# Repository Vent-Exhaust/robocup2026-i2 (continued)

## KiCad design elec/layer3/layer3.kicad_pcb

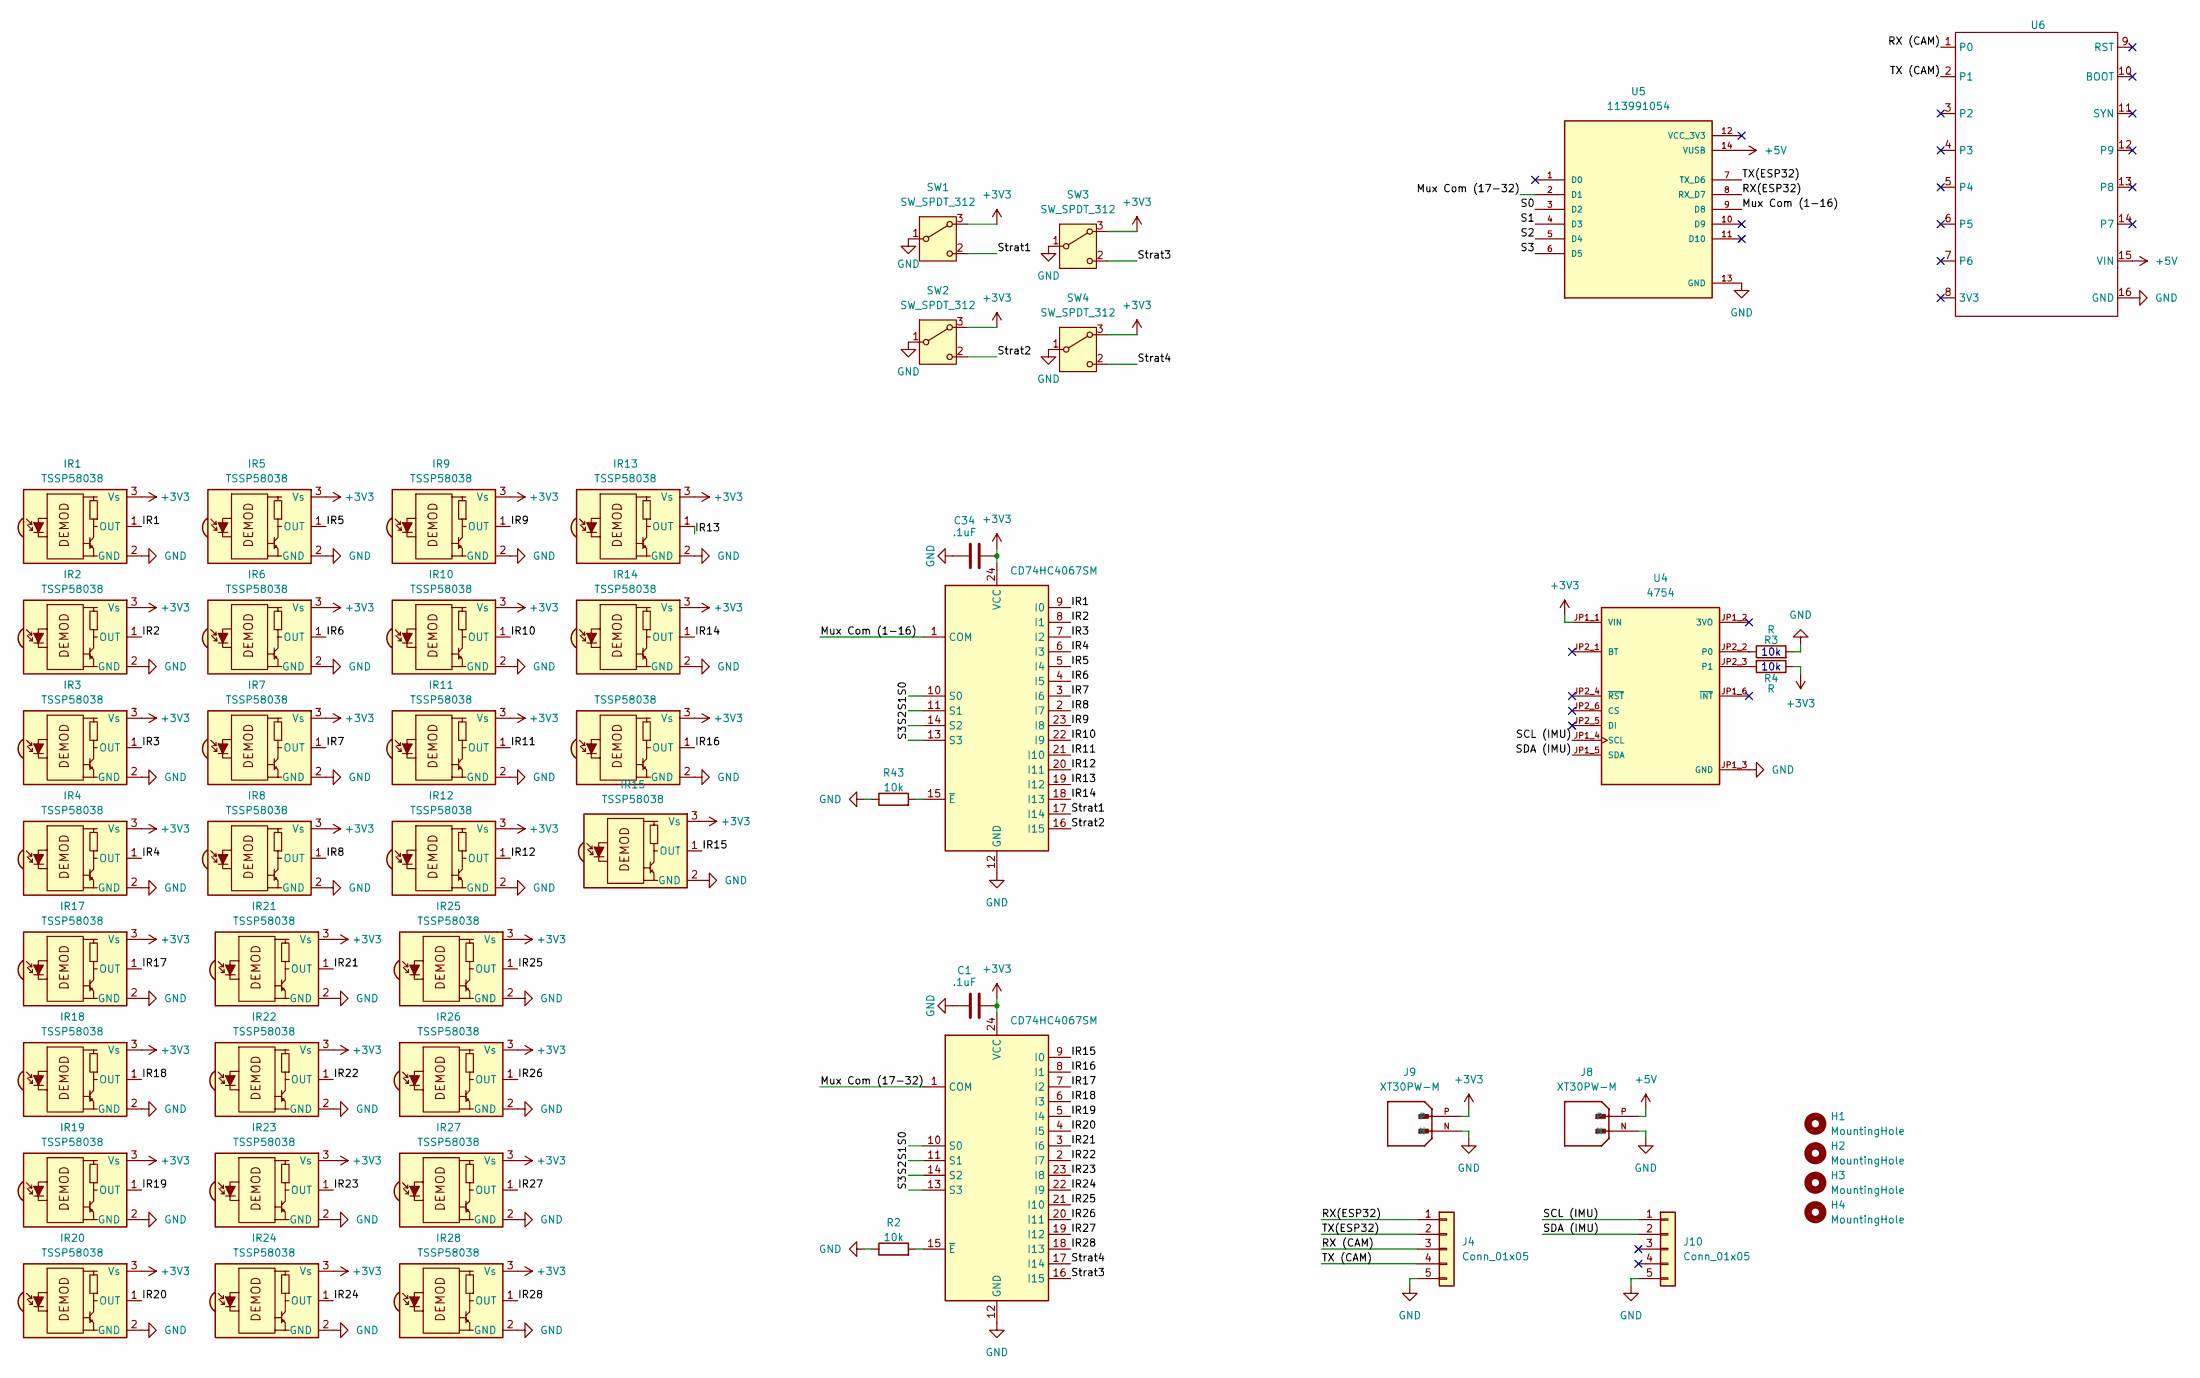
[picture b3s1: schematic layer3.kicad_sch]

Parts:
C1, C34: .1uF; C_0603_1608Metric
H1, H2, H3, H4: MountingHole; MountingHole_3.2mm_M3_DIN965_Pad
IR1, IR2, IR3, IR4, IR5, IR6, IR7, IR8, IR9, IR10, IR11, IR12, IR13, IR14, IR15, IR16, IR17, IR18, IR19, IR20, IR21, IR22, IR23, IR24, IR25, IR26, IR27, IR28: TSSP58038; Vishay_MINICAST-3Pin
J4, J10: Conn_01x05; JST_XH_B5B-XH-A_1x05_P2.50mm_Vertical
J8, J9: XT30PW-M; AMASS_XT30UPB-M_1x02_P5.0mm_Vertical; PARTREV 1.2
R2, R43: 10k; R_0603_1608Metric
R3, R4: R; R_0603_1608Metric_Pad0.98x0.95mm_HandSolder
SW1, SW2, SW3, SW4: SW_SPDT_312; SS12D00G3
U1, U2: CD74HC4067SM
U4: 4754; MODULE_4754; PARTREV 2021-03-16
U5: 113991054; XiaoSeeedStudioEsp32; PARTREV 23/05/2022
U6: OPENMV_M7

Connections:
+3V3: C1.2, C34.2, IR1.3 (Vs), IR2.3 (Vs), IR3.3 (Vs), IR4.3 (Vs), IR5.3 (Vs), IR6.3 (Vs), IR7.3 (Vs), IR8.3 (Vs), IR9.3 (Vs), IR10.3 (Vs), IR11.3 (Vs), IR12.3 (Vs), IR13.3 (Vs), IR14.3 (Vs), IR15.3 (Vs), IR16.3 (Vs), IR17.3 (Vs), IR18.3 (Vs), IR19.3 (Vs), IR20.3 (Vs), IR21.3 (Vs), IR22.3 (Vs), IR23.3 (Vs), IR24.3 (Vs), IR25.3 (Vs), IR26.3 (Vs), IR27.3 (Vs), IR28.3 (Vs), J9.P, R4.1, SW1.3 (A), SW2.3 (A), SW3.3 (A), SW4.3 (A), U1.24 (VCC), U2.24 (VCC), U4.JP1_1 (VIN)
+5V: J8.P, U5.14 (VUSB), U6.15 (VIN)
/IR1: IR1.1 (OUT), U2.9 (I0)
/IR2: IR2.1 (OUT), U2.8 (I1)
/IR3: IR3.1 (OUT), U2.7 (I2)
/IR4: IR4.1 (OUT), U2.6 (I3)
/IR5: IR5.1 (OUT), U2.5 (I4)
/IR6: IR6.1 (OUT), U2.4 (I5)
/IR7: IR7.1 (OUT), U2.3 (I6)
/IR8: IR8.1 (OUT), U2.2 (I7)
/IR9: IR9.1 (OUT), U2.23 (I8)
/IR10: IR10.1 (OUT), U2.22 (I9)
/IR11: IR11.1 (OUT), U2.21 (I10)
/IR12: IR12.1 (OUT), U2.20 (I11)
/IR13: IR13.1 (OUT), U2.19 (I12)
/IR14: IR14.1 (OUT), U2.18 (I13)
/IR15: IR15.1 (OUT), U1.9 (I0)
/IR16: IR16.1 (OUT), U1.8 (I1)
/IR17: IR17.1 (OUT), U1.7 (I2)
/IR18: IR18.1 (OUT), U1.6 (I3)
/IR19: IR19.1 (OUT), U1.5 (I4)
/IR20: IR20.1 (OUT), U1.4 (I5)
/IR21: IR21.1 (OUT), U1.3 (I6)
/IR22: IR22.1 (OUT), U1.2 (I7)
/IR23: IR23.1 (OUT), U1.23 (I8)
/IR24: IR24.1 (OUT), U1.22 (I9)
/IR25: IR25.1 (OUT), U1.21 (I10)
/IR26: IR26.1 (OUT), U1.20 (I11)
/IR27: IR27.1 (OUT), U1.19 (I12)
/IR28: IR28.1 (OUT), U1.18 (I13)
/Mux Com (1-16): U2.1 (COM), U5.9 (D8)
/Mux Com (17-32): U1.1 (COM), U5.2 (D1)
/RX (CAM): J4.3, U6.1 (P0)
/RX(ESP32): J4.1, U5.8 (RX_D7)
/S0: U1.10 (S0), U2.10 (S0), U5.3 (D2)
/S1: U1.11 (S1), U2.11 (S1), U5.4 (D3)
/S2: U1.14 (S2), U2.14 (S2), U5.5 (D4)
/S3: U1.13 (S3), U2.13 (S3), U5.6 (D5)
/SCL (IMU): J10.1, U4.JP1_4 (SCL)
/SDA (IMU): J10.2, U4.JP1_5 (SDA)
/Strat1: SW1.2 (C), U2.17 (I14)
/Strat2: SW2.2 (C), U2.16 (I15)
/Strat3: SW3.2 (C), U1.16 (I15)
/Strat4: SW4.2 (C), U1.17 (I14)
/TX (CAM): J4.4, U6.2 (P1)
/TX(ESP32): J4.2, U5.7 (TX_D6)
GND: C1.1, C34.1, IR1.2 (GND), IR2.2 (GND), IR3.2 (GND), IR4.2 (GND), IR5.2 (GND), IR6.2 (GND), IR7.2 (GND), IR8.2 (GND), IR9.2 (GND), IR10.2 (GND), IR11.2 (GND), IR12.2 (GND), IR13.2 (GND), IR14.2 (GND), IR15.2 (GND), IR16.2 (GND), IR17.2 (GND), IR18.2 (GND), IR19.2 (GND), IR20.2 (GND), IR21.2 (GND), IR22.2 (GND), IR23.2 (GND), IR24.2 (GND), IR25.2 (GND), IR26.2 (GND), IR27.2 (GND), IR28.2 (GND), J4.5, J8.N, J9.N, J10.5, R2.1, R3.2, R43.1, SW1.1 (B), SW2.1 (B), SW3.1 (B), SW4.1 (B), U1.12 (GND), U2.12 (GND), U4.JP1_3 (GND), U5.13 (GND), U6.16 (GND)
unnamed: R2.2, U1.15 (~E)
unnamed: R43.2, U2.15 (~E)
unnamed: R3.1, U4.JP2_2 (P0)
unnamed: R4.2, U4.JP2_3 (P1)

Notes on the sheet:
10k

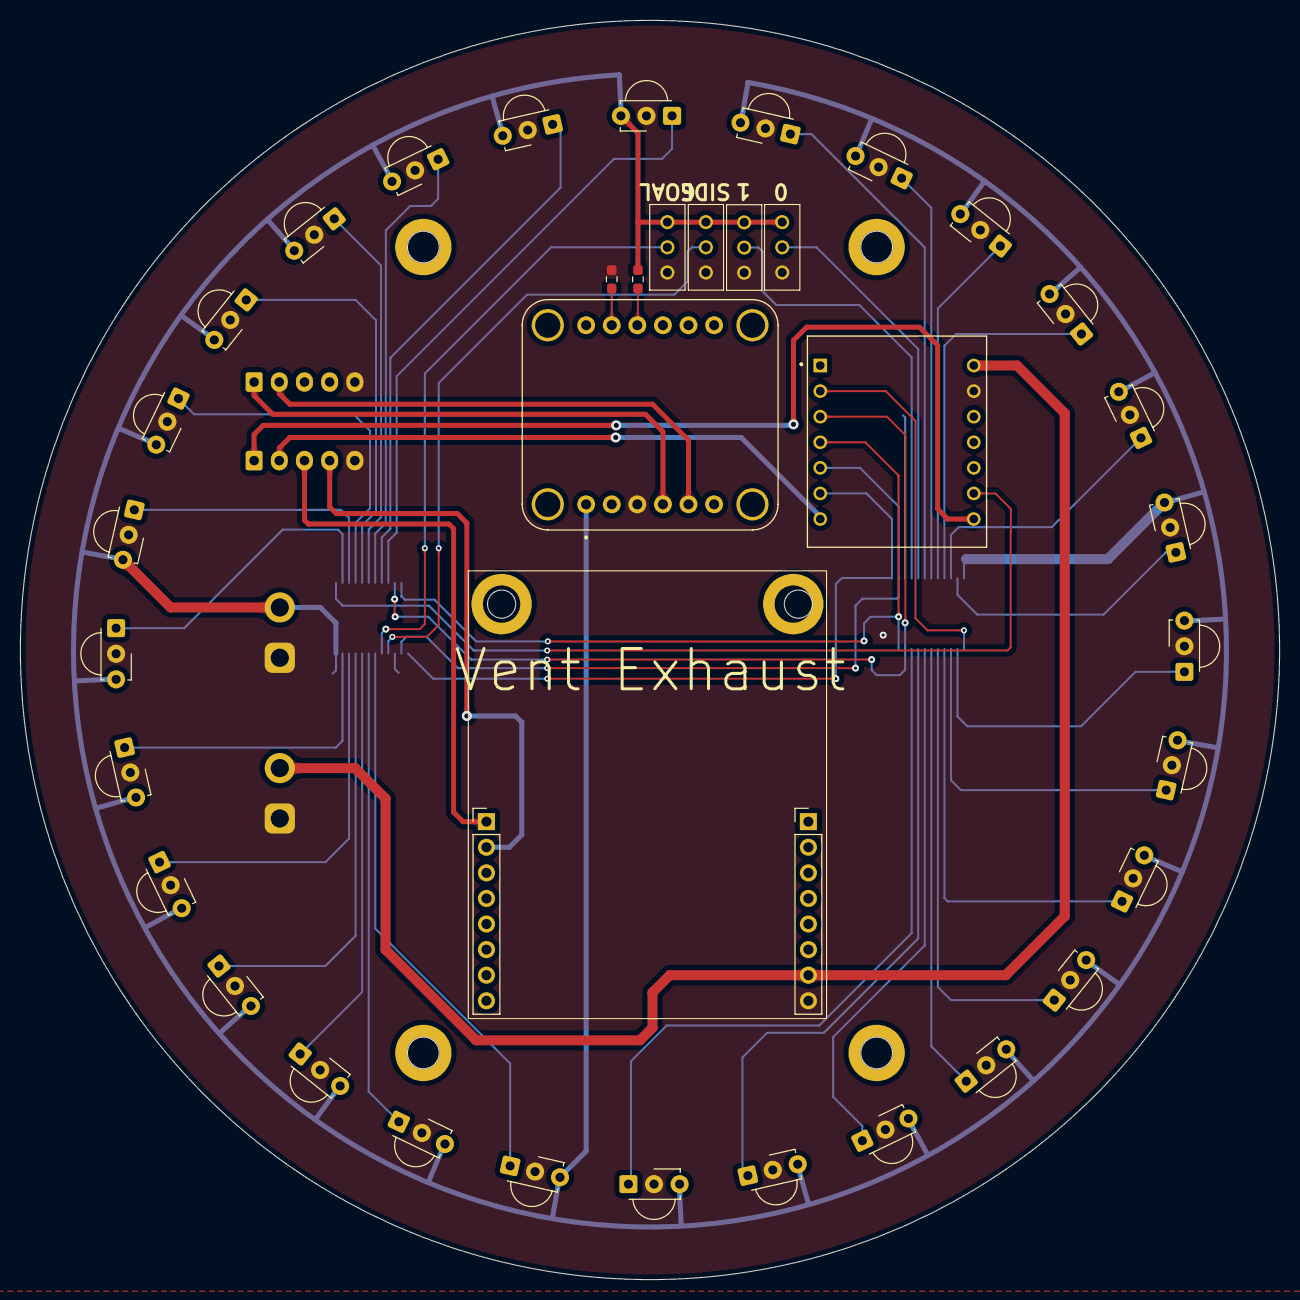
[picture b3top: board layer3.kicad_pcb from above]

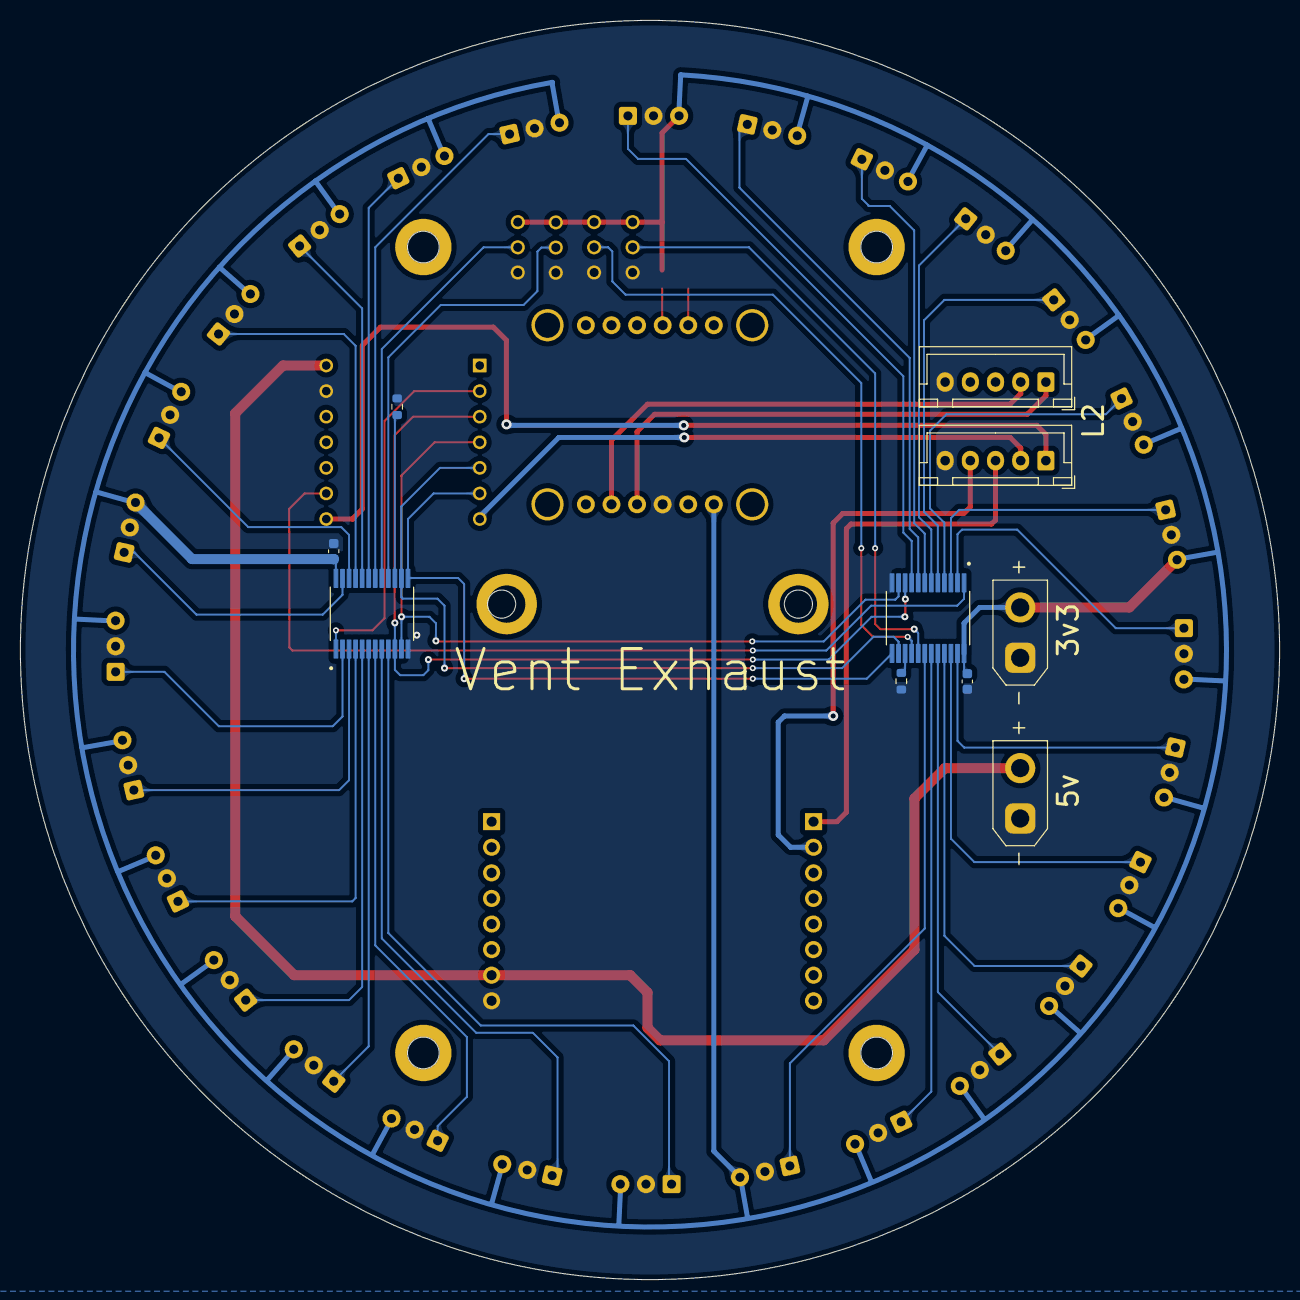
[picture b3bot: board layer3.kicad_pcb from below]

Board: 2 copper layers, 125.0 x 125.0 mm, 51 parts (10 on the bottom side), 51 nets.

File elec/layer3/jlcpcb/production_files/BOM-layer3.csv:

Comment,Designator,Footprint,LCSC,Quantity
.1uF,"C1,C34",C_0603_1608Metric,C1591,2
10k,"R2,R43",R_0603_1608Metric,C25804,2
CD74HC4067SM,"U1,U2",CD74HC4067SM,C98457,2
R,"R3,R4",R_0603_1608Metric_Pad0.98x0.95mm_HandSolder,C25804,2
113991054,U5,XiaoSeeedStudioEsp32,,1
~,U6,OPENMV_M7,,1
XT30PW-M,J8,AMASS_XT30UPB-M_1x02_P5.0mm_Vertical,,1
4754,U4,MODULE_4754,,1
XT30PW-M,J9,AMASS_XT30UPB-M_1x02_P5.0mm_Vertical,,1
TSSP58038,IR1,Vishay_MINICAST-3Pin,,1
Conn_01x05,J10,JST_XH_B5B-XH-A_1x05_P2.50mm_Vertical,,1
Conn_01x05,J4,JST_XH_B5B-XH-A_1x05_P2.50mm_Vertical,,1
SW_SPDT_312,SW2,SS12D00G3,,1
SW_SPDT_312,SW4,SS12D00G3,,1
SW_SPDT_312,SW1,SS12D00G3,,1
SW_SPDT_312,SW3,SS12D00G3,,1
TSSP58038,IR11,Vishay_MINICAST-3Pin,,1
TSSP58038,IR23,Vishay_MINICAST-3Pin,,1
TSSP58038,IR28,Vishay_MINICAST-3Pin,,1
TSSP58038,IR8,Vishay_MINICAST-3Pin,,1
TSSP58038,IR19,Vishay_MINICAST-3Pin,,1
TSSP58038,IR24,Vishay_MINICAST-3Pin,,1
TSSP58038,IR3,Vishay_MINICAST-3Pin,,1
TSSP58038,IR15,Vishay_MINICAST-3Pin,,1
TSSP58038,IR16,Vishay_MINICAST-3Pin,,1
TSSP58038,IR14,Vishay_MINICAST-3Pin,,1
TSSP58038,IR9,Vishay_MINICAST-3Pin,,1
TSSP58038,IR5,Vishay_MINICAST-3Pin,,1
TSSP58038,IR27,Vishay_MINICAST-3Pin,,1
TSSP58038,IR25,Vishay_MINICAST-3Pin,,1
TSSP58038,IR10,Vishay_MINICAST-3Pin,,1
TSSP58038,IR12,Vishay_MINICAST-3Pin,,1
TSSP58038,IR17,Vishay_MINICAST-3Pin,,1
TSSP58038,IR22,Vishay_MINICAST-3Pin,,1
TSSP58038,IR20,Vishay_MINICAST-3Pin,,1
TSSP58038,IR4,Vishay_MINICAST-3Pin,,1
TSSP58038,IR7,Vishay_MINICAST-3Pin,,1
TSSP58038,IR2,Vishay_MINICAST-3Pin,,1
TSSP58038,IR18,Vishay_MINICAST-3Pin,,1
TSSP58038,IR6,Vishay_MINICAST-3Pin,,1
TSSP58038,IR26,Vishay_MINICAST-3Pin,,1
TSSP58038,IR13,Vishay_MINICAST-3Pin,,1
TSSP58038,IR21,Vishay_MINICAST-3Pin,,1

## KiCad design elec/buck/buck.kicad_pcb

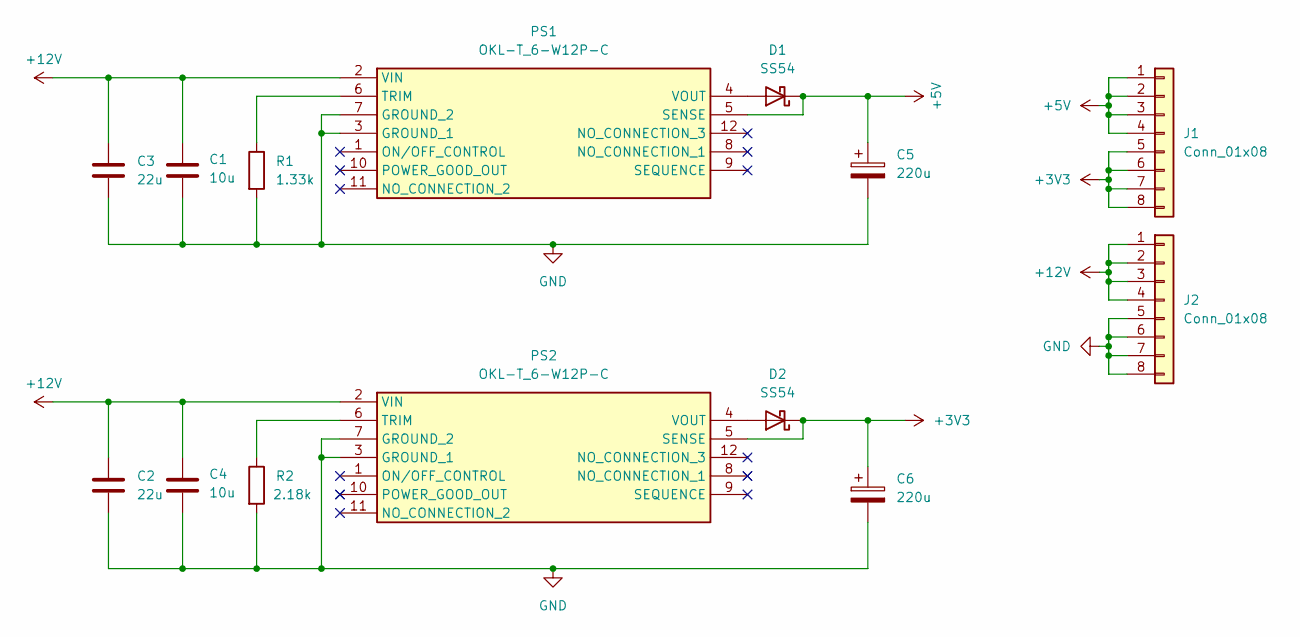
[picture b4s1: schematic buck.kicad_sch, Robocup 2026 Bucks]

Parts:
C1, C4: 10u; C_0603_1608Metric
C2, C3: 22u; C_0603_1608Metric
C5, C6: 220u; CP_EIA-7343-15_Kemet-W_HandSolder
D1, D2: SS54
J1, J2: Conn_01x08; PinHeader_1x08_P2.54mm_Vertical
PS1, PS2: OKL-T_6-W12P-C; MURATA_OKL-T-6-W12; Mouser Part Number 580-OKL-T/6-W12P-C
R1: 1.33k; R_0603_1608Metric
R2: 2.18k; R_0603_1608Metric

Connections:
+3V3: C6.1, D2.1 (K), J1.5, J1.6, J1.7, J1.8, PS2.5 (SENSE)
+5V: C5.1, D1.1 (K), J1.1, J1.2, J1.3, J1.4, PS1.5 (SENSE)
+12V: C1.1, C2.1, C3.1, C4.1, J2.1, J2.2, J2.3, J2.4, PS1.2 (VIN), PS2.2 (VIN)
GND: C1.2, C2.2, C3.2, C4.2, C5.2, C6.2, J2.5, J2.6, J2.7, J2.8, PS1.3 (GROUND_1), PS1.7 (GROUND_2), PS2.3 (GROUND_1), PS2.7 (GROUND_2), R1.2, R2.2
unnamed: D1.2 (A), PS1.4 (VOUT)
unnamed: D2.2 (A), PS2.4 (VOUT)
unnamed: PS1.6 (TRIM), R1.1
unnamed: PS2.6 (TRIM), R2.1

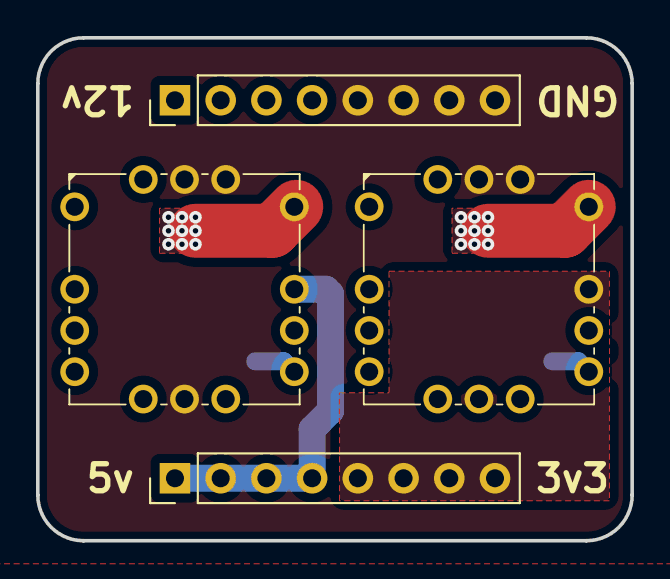
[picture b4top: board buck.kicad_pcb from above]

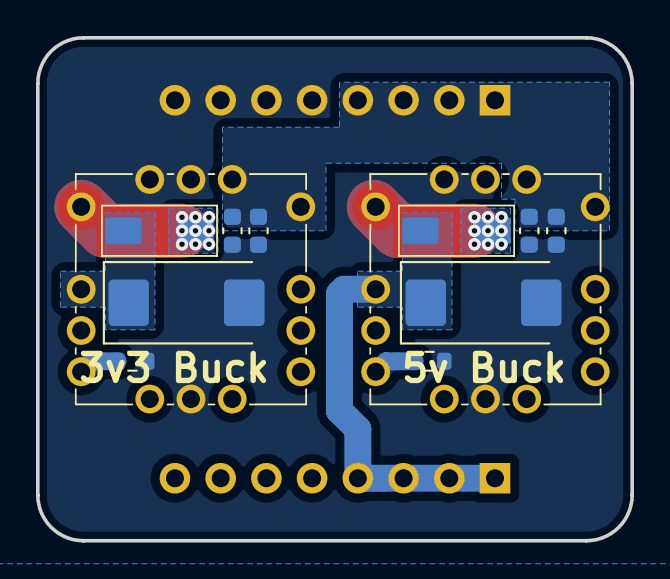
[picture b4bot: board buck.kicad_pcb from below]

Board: 2 copper layers, 33.0 x 27.9 mm, 14 parts (10 on the bottom side), 8 nets.

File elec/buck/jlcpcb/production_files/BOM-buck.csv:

Comment,Designator,Footprint,LCSC,Quantity
1.33k,R1,R_0603_1608Metric,C22838,1
10u,"C1,C4",C_0603_1608Metric,C1691,2
2.18k,R2,R_0603_1608Metric,C862654,1
220u,"C5,C6",CP_EIA-7343-15_Kemet-W_HandSolder,C8024,2
22u,"C2,C3",C_0603_1608Metric,C59461,2
SS54,"D1,D2",SS54,C22452,2

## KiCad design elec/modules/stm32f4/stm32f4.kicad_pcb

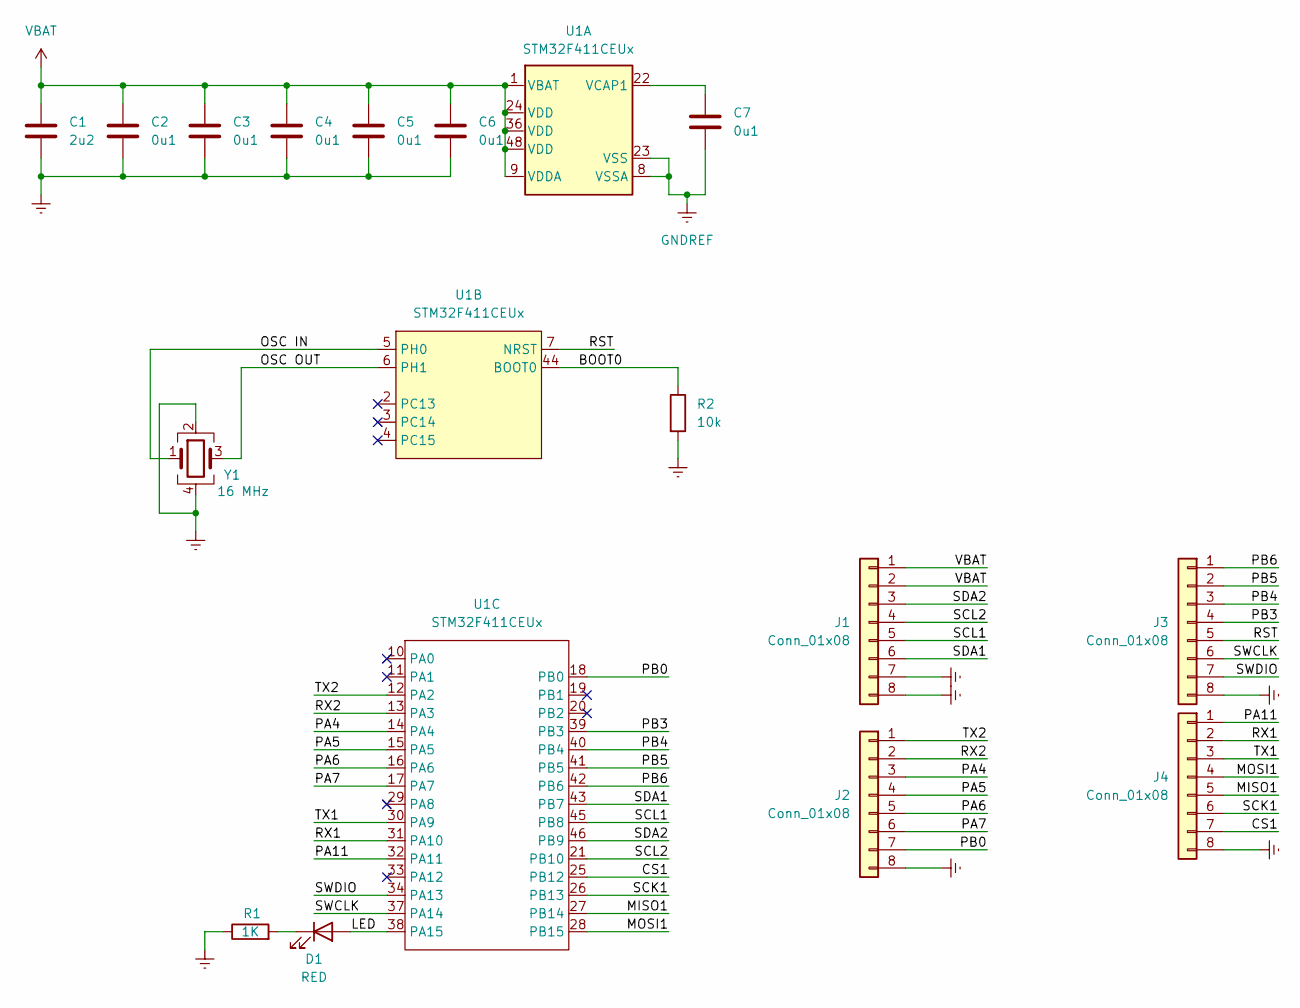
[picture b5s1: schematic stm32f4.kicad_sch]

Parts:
C1: 2u2; cap0603
C2, C3, C4, C5, C6, C7: 0u1; cap0603
D1: RED; led0603
J1, J2, J3, J4: Conn_01x08; PinHeader_1x08_P2.54mm_Vertical
R1: 1K; res0603
R2: 10k; res0603
U1: STM32F411CEUx; QFN-48-1EP_7x7mm_P0.5mm_EP5.6x5.6mm
Y1: 16 MHz; CX3225SB16000D0FPLCC

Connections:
/BOOT0: R2.1, U1.44 (BOOT0)
/CS1: J4.7, U1.25 (PB12)
/LED: D1.2 (A), U1.38 (PA15)
/MISO1: J4.5, U1.27 (PB14)
/MOSI1: J4.4, U1.28 (PB15)
/OSC IN: U1.5 (PH0), Y1.1
/OSC OUT: U1.6 (PH1), Y1.3
/PA4: J2.3, U1.14 (PA4)
/PA5: J2.4, U1.15 (PA5)
/PA6: J2.5, U1.16 (PA6)
/PA7: J2.6, U1.17 (PA7)
/PA11: J4.1, U1.32 (PA11)
/PB0: J2.7, U1.18 (PB0)
/PB3: J3.4, U1.39 (PB3)
/PB4: J3.3, U1.40 (PB4)
/PB5: J3.2, U1.41 (PB5)
/PB6: J3.1, U1.42 (PB6)
/RST: J3.5, U1.7 (NRST)
/RX1: J4.2, U1.31 (PA10)
/RX2: J2.2, U1.13 (PA3)
/SCK1: J4.6, U1.26 (PB13)
/SCL1: J1.5, U1.45 (PB8)
/SCL2: J1.4, U1.21 (PB10)
/SDA1: J1.6, U1.43 (PB7)
/SDA2: J1.3, U1.46 (PB9)
/SWCLK: J3.6, U1.37 (PA14)
/SWDIO: J3.7, U1.34 (PA13)
/TX1: J4.3, U1.30 (PA9)
/TX2: J2.1, U1.12 (PA2)
unnamed: D1.1 (K), R1.2
unnamed: C7.1, U1.22 (VCAP1)
VBAT: C1.1, C2.1, C3.1, C4.1, C5.1, C6.1, J1.1, J1.2, U1.1 (VBAT), U1.9 (VDDA), U1.24 (VDD), U1.36 (VDD), U1.48 (VDD)

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
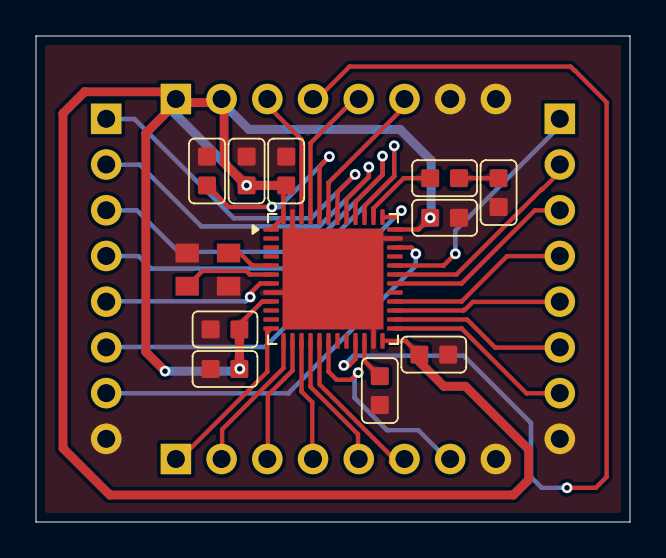
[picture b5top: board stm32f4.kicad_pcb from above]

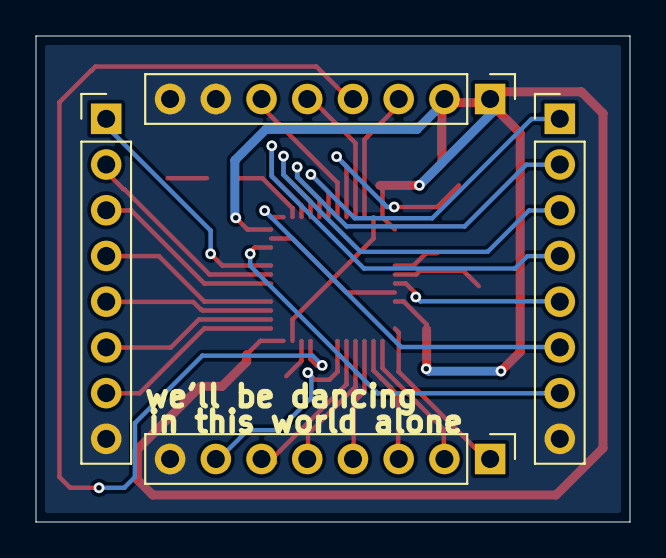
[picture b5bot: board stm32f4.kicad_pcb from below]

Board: 2 copper layers, 33.0 x 27.0 mm, 16 parts (4 on the bottom side), 33 nets.

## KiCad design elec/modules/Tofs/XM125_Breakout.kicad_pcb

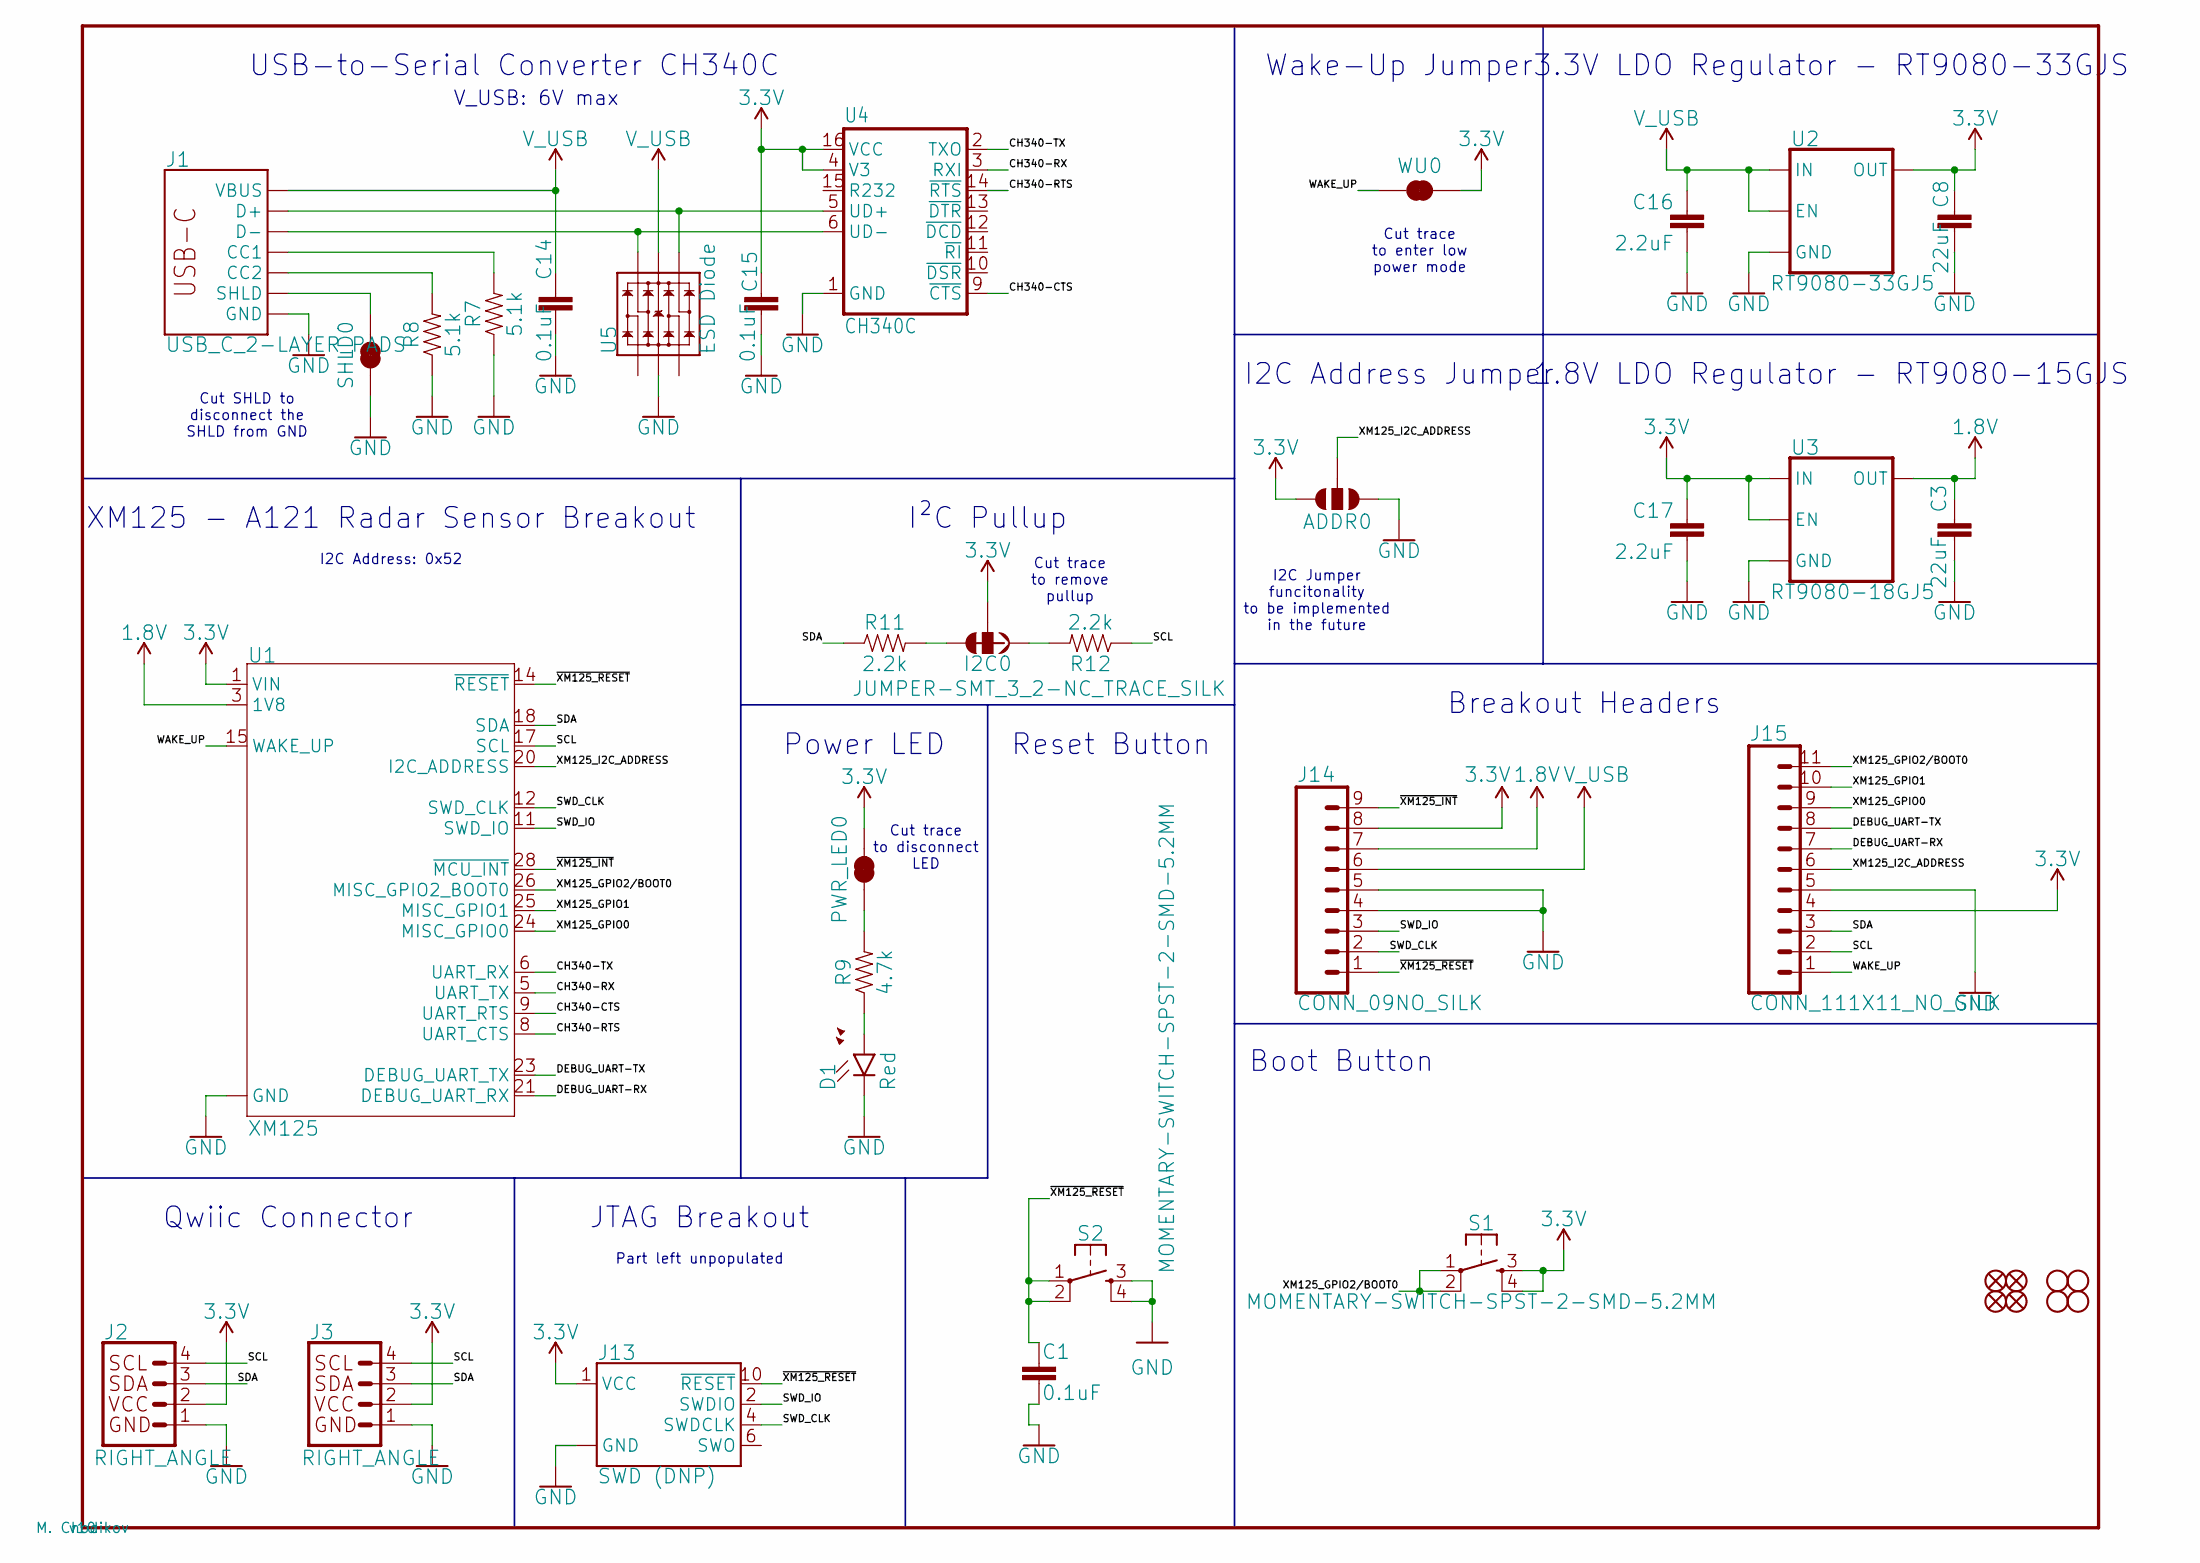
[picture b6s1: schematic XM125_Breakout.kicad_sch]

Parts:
ADDR0: JUMPER-SMT_3_NO_SILK; SMT-JUMPER_3_NO_SILK
C1, C14, C15: 0.1uF; 0603
C3, C8: 22uF; 0603
C16, C17: 2.2uF; 0603
D1: Red; LED-0603
FD1, FD2, FD3, FD4: FIDUCIAL1X2; FIDUCIAL-1X2
FRAME2: FRAME-LETTER; CREATIVE_COMMONS
H1, H2, H3, H4: STAND-OFF
I2C0: JUMPER-SMT_3_2-NC_TRACE_SILK; SMT-JUMPER_3_2-NC_TRACE_SILK
J1: USB_C_2-LAYER_PADS; USB-C-16P-2LAYER-PADS
J2, J3: RIGHT_ANGLE; JST04_1MM_RA
J13: SWD (DNP); 2X5-SMD-UNSHROUDED_DNP_NO_PASTE
J14: CONN_09NO_SILK; 1X09_NO_SILK
J15: CONN_111X11_NO_SILK; 1X11_NO_SILK
PWR_LED0: JUMPER-SMT_2_NC_TRACE_SILK; SMT-JUMPER_2_NC_TRACE_SILK
R7, R8: 5.1k; 0603
R9: 4.7k; 0603
R11, R12: 2.2k; 0603
S1, S2: MOMENTARY-SWITCH-SPST-2-SMD-5.2MM; TACTILE_SWITCH_SMD_5.2MM
SHLD0: JUMPER-SMT_2_NC_TRACE_SILK; SMT-JUMPER_2_NC_TRACE_SILK
U1: XM125; XM125_ACC
U2: RT9080-33GJ5; SOT23-5
U3: RT9080-18GJ5; SOT23-5
U4: CH340C; SO016
U5: ESD Diode; SOT-23-6
WU0: JUMPER-SMT_2_NC_TRACE_SILK; SMT-JUMPER_2_NC_TRACE_SILK

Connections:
1.8V: C3.1, J14.7, U1.3 (1V8), U3.5 (OUT)
3.3V: ADDR0.3, C8.1, C15.1, C17.1, I2C0.2, J2.2, J3.2, J13.1 (VCC), J14.8, J15.4, PWR_LED0.2, S1.3, S1.4, U1.1 (VIN), U2.5 (OUT), U3.1 (IN), U3.3 (EN), U4.4 (V3), U4.16 (VCC), WU0.2
CH340-CTS: U1.9 (UART_RTS), U4.9 (~CTS)
CH340-RTS: U1.8 (UART_CTS), U4.14 (~RTS)
CH340-RX: U1.5 (UART_TX), U4.3 (RXI)
CH340-TX: U1.6 (UART_RX), U4.2 (TXO)
DEBUG_UART-RX: J15.7, U1.21 (DEBUG_UART_RX)
DEBUG_UART-TX: J15.8, U1.23 (DEBUG_UART_TX)
GND: ADDR0.1, C1.1, C3.2, C8.2, C14.2, C15.2, C16.2, C17.2, D1.C, J1.GND, J1.GND2 (GND), J2.1, J3.1, J13.3 (GND), J13.5 (GND), J13.9 (GND), J14.4, J14.5, J15.5, R7.1, R8.1, S2.3, S2.4, SHLD0.1, U1.2 (GND), U1.4 (GND), U1.7 (GND), U1.10 (GND), U1.13 (GND), U1.16 (GND), U1.19 (GND), U1.22 (GND), U1.27 (GND), U2.2 (GND), U3.2 (GND), U4.1 (GND), U5.2 (VSS)
unnamed: J1.A6 (D+), J1.B6 (D+), U4.5 (UD+), U5.4 (IO3)
unnamed: J1.A7 (D-), J1.B7 (D-), U4.6 (UD-), U5.6 (IO4)
unnamed: J1.SHLD1 (SHLD), J1.SHLD2 (SHLD), J1.SHLD3 (SHLD), J1.SHLD4 (SHLD), SHLD0.2
unnamed: J1.B5 (CC2), R8.2
unnamed: J1.A5 (CC1), R7.2
unnamed: PWR_LED0.1, R9.2
unnamed: D1.A, R9.1
unnamed: I2C0.3, R11.2
unnamed: I2C0.1, R12.2
SCL: J2.4, J3.4, J15.2, R12.1, U1.17 (SCL)
SDA: J2.3, J3.3, J15.3, R11.1, U1.18 (SDA)
SWD_CLK: J13.4 (SWDCLK), J14.2, U1.12 (SWD_CLK)
SWD_IO: J13.2 (SWDIO), J14.3, U1.11 (SWD_IO)
V_USB: C14.1, C16.1, J1.VBUS1 (VBUS), J1.VBUS2 (VBUS), J14.6, U2.1 (IN), U2.3 (EN), U5.5 (VCC)
WAKE_UP: J15.1, U1.15 (WAKE_UP), WU0.1
XM125_GPIO0: J15.9, U1.24 (MISC_GPIO0)
XM125_GPIO1: J15.10, U1.25 (MISC_GPIO1)
XM125_GPIO2/BOOT0: J15.11, S1.1, S1.2, U1.26 (MISC_GPIO2_BOOT0)
XM125_I2C_ADDRESS: ADDR0.2, J15.6, U1.20 (I2C_ADDRESS)
~XM125_INT: J14.9, U1.28 (~MCU_INT)
~XM125_RESET: C1.2, J13.10 (~RESET), J14.1, S2.1, S2.2, U1.14 (~RESET)

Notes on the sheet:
USB-to-Serial Converter CH340C
Wake-Up Jumper
Cut trace to disconnect LED
Cut SHLD to disconnect the SHLD from GND
Cut trace to enter low power mode
Breakout Headers
Cut trace to remove pullup
3.3V LDO Regulator - RT9080-33GJS
I2C Jumper funcitonality to be implemented in the future
I2C Address Jumper
I2C Address: 0x52
I²C Pullup
XM125 - A121 Radar Sensor Breakout
Reset Button
Part left unpopulated
Boot Button
JTAG Breakout
Qwiic Connector
V_USB: 6V max
1.8V LDO Regulator - RT9080-15GJS
Power LED

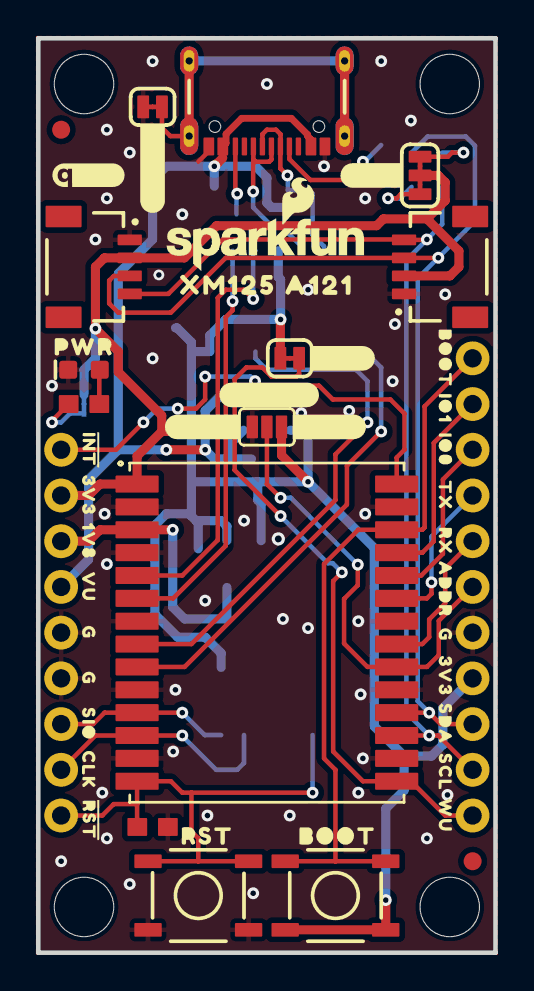
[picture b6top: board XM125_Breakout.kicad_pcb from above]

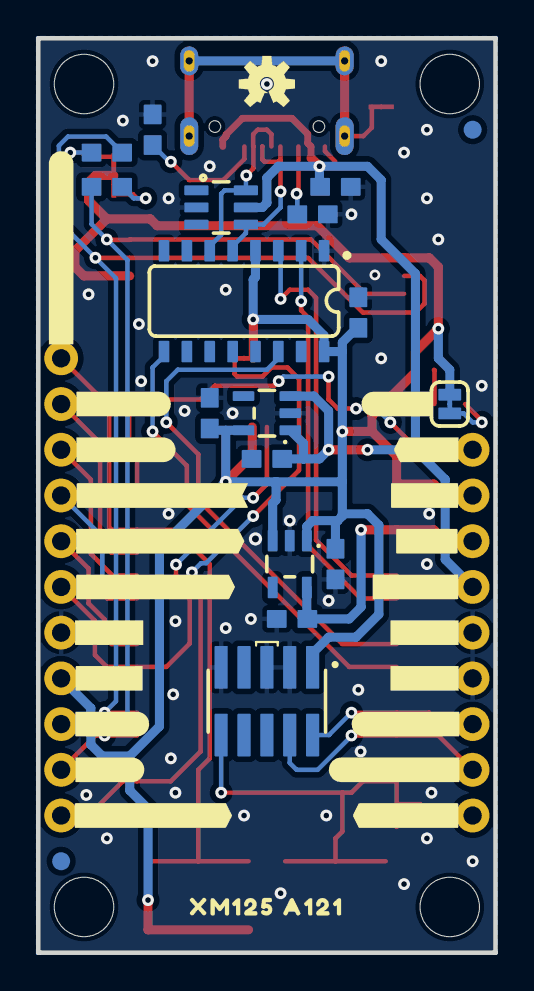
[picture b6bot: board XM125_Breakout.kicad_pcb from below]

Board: 2 copper layers, 25.4 x 50.8 mm, 95 parts (41 on the bottom side), 30 nets.

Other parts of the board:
LOGO1: SPECIAL_INSTRUCTIONS-ORDERING; ORDERING_INSTRUCTIONS
LOGO2: QWIIC_LOGO_4MM; QWIIC_4MM
LOGO4: OSHW-LOGOS; OSHW-LOGO-S
LOGO6: SFE_LOGO_NAME_FLAME.1_INCH; SFE_LOGO_NAME_FLAME_.1
U$1: #INT143
U$2: ##INT#2
U$3: #LED#139
U$4, U$30, U$31: #GND#141
U$5: RST1630063003525
U$6: RX1152
U$7: #SWDIO#4
U$8: #VUSB#1
U$9: #3V3#17
U$10: #SCL#8
U$11: BOOT21630063003532
U$12: PWR21630063003533
U$13: #SDA#9
U$14, U$33: 3V3144
U$15: 1V8144
U$16: #1V8#141
U$18: WU9
U$19: #RST6
U$20: #GPIO0#5
U$21: #GPIO1#5
U$22: #WU#14
U$23, U$32: #3V3#141
U$24: XM125_A1211163
U$25: #ADDR#16
U$26: #I2C#126
U$27: #GPIO2##BOOT#141
U$28: #DEBUG_RX#19
U$29: #SHLD#129
U$34, U$35, U$36: G144
U$38: VU146
U$39: IO0147
U$40: IO1148
U$41: BOOT1149
U$42: CLK1150
U$43: #SWDCLK#1151
U$44: TX1153
U$45: ADDR1154
U$46: SDA1155
U$47: SCL1157
U$48: #I2C_ADDR#12
U$49: SIO1159
U$50: #GND#17
U$51: #DEBUG_TX#18
U$54: XM125_A1211167
U$55: #WAKE_UP#12
U$56: ##RESET#13

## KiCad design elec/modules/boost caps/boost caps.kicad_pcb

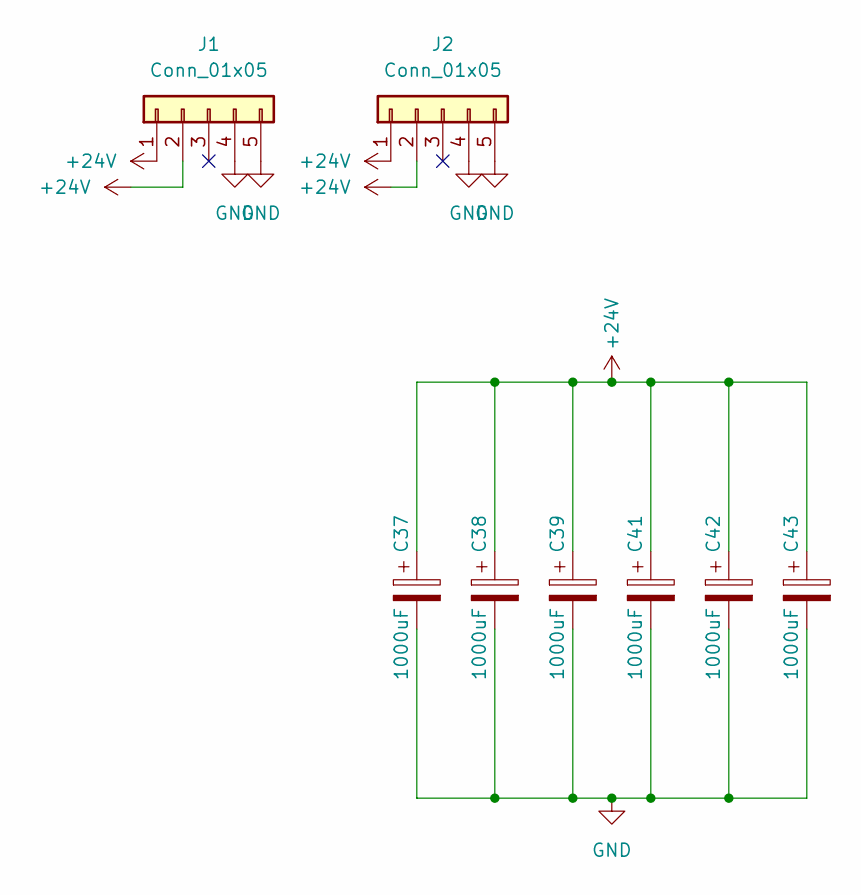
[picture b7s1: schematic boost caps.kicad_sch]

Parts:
C37, C38, C39, C41, C42, C43: 1000uF; CP_Radial_D16.0mm_P7.50mm; LCSC C249586
J1, J2: Conn_01x05; PinHeader_1x05_P2.54mm_Vertical

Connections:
+24V: C37.1, C38.1, C39.1, C41.1, C42.1, C43.1, J1.1, J1.2, J2.1, J2.2
GND: C37.2, C38.2, C39.2, C41.2, C42.2, C43.2, J1.4, J1.5, J2.4, J2.5

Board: 2 copper layers, 8 parts (0 on the bottom side), 2 nets, no tracks yet.
